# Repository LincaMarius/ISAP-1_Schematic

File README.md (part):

# ISAP-1 Computer Schematic
The ISAP-1 computer is the improved version of the SAP-1 computer made by me.

ISAP Computer stands for Improved Simple as Possible Computer

This is the stage of choosing the electronic components used to make the ISAP-1 computer and designing the Schematic.

By: Lincă Marius Gheorghe

https://github.com/LincaMarius

## About the project, brief description
The goal of this project is to create a more efficient version of the SAP (Simple As Possible) computer, but with minimal changes so that the instruction format remains the same.

This project is part of a project made by me:
https://github.com/LincaMarius/ISAP-Computer

where I optimized the SAP-1 computer

## ISAP-1 TTL Computer version 0.1
Version 0.1 of the ISAP-1 computer is based on the original SAP-1 computer schematic.

The structure of the SAP-1 computer and by implication the ISAP-1 computer is:

I want to make the ISAP-1 computer in modular form. So I modified the Structural Diagram like this:

It turns out that we will have the following modules:
- Reset and Clock
- ISAP-1 CPU
- Control Unit
- RAM Memory
- Output Display
- Back Plane

The SAP-1 computer was designed using 7400 series TTL chips in the LS (Low-Power Schottky) variant. Since version 0.1 of the ISAP-1 computer will be an almost identical copy of the SAP-1 computer, I will still use TTL technology.

I will keep the chip numbering order according to the original schematic of the SAP-1 computer.

### Central Processing Unit Schematic
The first module designed is the Central Processing Unit module.

The original block diagram of the Central Processing Unit of the SAP-1 computer and implicitly of the ISAP-1 computer is:

Initially, I used Altium Designer to design the Schematic and PCB.

But, so that this schematic can be viewed and possibly edited by anyone, I put the version edited with KiCAD on GitHub, because this program is free and can be freely used by anyone.

The implemented schematic will be almost identical to the original one of the SAP-1 Computer.

In the original schematic the chips are labeled C1 to C48. To eliminate confusion with the capacitor notation I have used the chip notation U1 to U49 as is used in modern days.

First I will implement the Central Processing Unit which has the following schematic:

You can see all the functional blocks in the diagram in figure 51. In addition I added decoupling capacitors for the power supply circuit. We also have the J1M connectors for connecting to the supply voltage given by the Back Plane, the J2M connector for connecting to the three system buses located on the Back Plane. The J3F and J4F connectors are used to allow the Control Block module to be attached to the CPU module.

#### Program Counter Schematic
In the original schematic, the authors used 4 Flip-Flops connected in such a way that they form a Binary Counter. For implementation, two 74LS107 were used for this purpose.

Counting is done when the CP control signal is active and the falling edge of the clock signal appears.

This action occurs for any instruction during [ microstep T2 ](https://github.com/LincaMarius/ISAP-1_Instruction_Set/blob/main/Pictures/Figure3.png).

The Program Counter has its output connected to the Bus, therefore it must be Tri-State. A 74LS126 chip is used for this purpose

The output is active only when the EP control signal is high.

This action occurs for any instruction during [ microstep T1 ](https://github.com/LincaMarius/ISAP-1_Instruction_Set/blob/main/Pictures/Figure3.png).

The Schematic does has no changes from the original one.

The original schematic has no decoupling capacitors for the chips. For the computer's operating speed of 1kHz this may not matter.

I added a 100nF decoupling capacitor for each chip used in order to eliminate high-frequency noise propagation along the power supply path.

#### Address Register Schematic
In the original schematic, the authors used a 4-bit register using the 74LS173 chip which has a permanently active output.

Note that the connection of the inputs to the data bus is in reverse order in the original SAP-1 computer schematic, D0 is connected to pin 11, D1 is connected to pin 12, D2 is connected to pin 13 and D4 is connected to pin 14.

The outputs are also connected in the reverse order. The operation of the SAP-1 computer is not affected by this order because the correspondence between inputs and outputs is maintained.

The current schematic has no changes from the original schematic.

I added a 100nF decoupling capacitor to the chip used in order to eliminate high-frequency noise propagation on the power supply path.

#### Instruction Register Schematic
The Instruction Register is made using two integrated circuits of the 74LS173 type which is a 4-bit register.

The first chip marked U8 in the diagram stores the upper nibble which represents the binary code of the instruction being executed.

The second chip marked in the diagram U9 stores the lower nibble which represents the parameter for the instruction being executed.

According to the datasheet for the 74LS173 chip, pin 14 is D0 and the corresponding output Q0 is pin 3, pin 13 is D1 and the corresponding output Q1 is pin 4, pin 12 is D2 and the corresponding output Q2 is pin 4, and pin 11 is D3 and the corresponding output Q3 is pin 6.

But in the SAP-1 computer schematic, pin 14 which is D0 and pin 3 which is Q0 are connected to bit 3 of the W Bus, pin 13 which is D1 and pin 4 which is Q1 are connected to bit 2 of the W Bus, pin 12 which is D2 and pin 5 which is Q2 are connected to bit 1 of the W Bus and pin 11 which is D3 and pin 6 which is Q3 are connected to bit 0 of the W Bus.

So, the order of inputs and outputs is reversed. Since the inputs and outputs are also reversed accordingly, the operation of the SAP-1 computer is normal.

The schematic does not present any changes from the original.

I added a 100nF decoupling capacitor for each chip used in order to eliminate high-frequency noise propagation along the power supply path.

#### Accumulator Register Schematic
The Accumulator register is made using two 4-bit 74LS173 type registers marked U10 and U11 in the diagram (in the original diagram they are marked C10 and C11).

Pin 1 and pin 2 are connected to ground which causes the outputs to be permanently active. Thus, the contents of the Accumulator Register are permanently transmitted to the ALU via signals AD0 to AD7.

The contents of the Accumulator Register are put on the bus when the EA control signal is active, which activates the 8 Tri-State drivers. The Tri-State drivers are implemented using two 74LS126 chips, each containing 4 Tri-State drivers.

As in the previous cases, the order of inputs and outputs is reversed from the order of the bits on the W bus. Since the inputs and outputs are also reversed accordingly, the operation of the SAP-1 computer is normal.

The schematic has no changes from the original.

I added a 100nF decoupling capacitor for each chip used in order to eliminate high-frequency noise propagation along the power supply path.

#### Adder / Subtractor Schematic
The SAP-1 computer has no Logic Unit, it can only perform the Addition and Subtraction operations.

The main element of the Arithmetic Unit is the 74LS83 chip which is a 4-bit Full Adder, so two such chips are used.

The Subtract Operation is performed by 2's Complementing the operand B. For this purpose, 8 x XOR Gates are used. Each 74LS86 chip has 4 gates, so 2 chips are used.

The result is transmitted on the Bus via 8 three-state buffers when the EU control signal is active. These buffers are of the 74LS126 type. Each chip has 4 buffers, so 2 chips are required.

The schematic has no changes from the original.

I added a 100nF decoupling capacitor for each chip used in order to eliminate high-frequency noise propagation along the power supply path.

#### Register B Schematic
Register B acts as a temporary storage register, where the operand B required by the Adder to perform the Addition operation is loaded.

In the original schematic, two 4-bit 74LS173 type registers labeled C20 and C21 are used.

When the LB control signal is low and the rising edge of the clock signal occurs, the data present on the Bus is loaded into the registers.

The output is connected to input B of the Adder and is permanently enabled by connecting pins 1 and 2 to ground.

The schematic has no changes from the original.

I added a 100nF decoupling capacitor for each chip used in order to eliminate high-frequency noise propagation along the power supply path.

The archived project for ISAP-1 TTL Computer version 0.1 is here: \
https://github.com/LincaMarius/ISAP-1_Schematic/blob/main/KiCAD/ ISAP-1_TTL_CPU_1_0.zip

### Control Unit Schematic
The Control Unit's role is to direct the flow of data between the various Blocks of the Computer to ensure its operation and achieve the expected results.

It consists of three elements: the Instruction Decoder, the Ring Counter and the Control Matrix as can be seen in figure 14:

### Output Device – Binary Display
In the SAP-1 computer the output device is called the Output Register and is present in the Block Diagram at the bottom right of the drawing.

The Binary Display is made with 8 LEDs connected directly to the output of the Output Register.

### Output Device Schematic
In the original schematic, two 4-bit 74LS173 registers are used, denoted C22 and C23.

When the I/O control signal (the original LO) is low and the rising edge of the clock signal appears, the data present on the Bus is loaded into the registers.

The output is permanently active because pins 1 and 2 are connected to ground. The outputs are labeled O0 to O7.

I added the connectors marked J2_1 and J2_2 for connection to the Base PCB in case the Binary Display PCB separates from the computer PCB.

The schematic does not present any other changes compared to the original one.

### Binary Display Schematic
The Binary Display consists of eight LEDs connected to eight current limiting resistors of 1k ohm each.

The current is limited by resistors for a red LED to the value of (Voh – Vled) / (R + Rint) = (2.4V – 1.8V) / (1000 + 100) = 0.5 / 1100 = 0.5mA (theoretical).

I added the connectors marked J2_1 and J2_2 for connection to the Base PCB in case the Binary Display PCB separates from the computer PCB.

The schematic does not present any other changes compared to the original one.

### Front Panel Schematic
The Front Panel provides the user interface. Contains the Reset circuit, Manual/Automatic mode selector, Step button, main clock.

I added two connectors marked J5_1 and J5_2 for connection to the Base PCB in case the Front Panel PCB is separated and used separately from the ISAP-1 computer PCB.

The switches can be mounted on this PCB or mounted on a Front Panel and connected via wires.

The schematic does not present any other changes compared to the original one.

The switches used to set the Memory in Programming mode must also be placed on the Front Panel.

The switches can be mounted on this module or mounted on a Front Panel and connected via wires.

### Control Unit Schematic
The Control Unit's role is to direct the flow of data between the various Blocks of the Computer to ensure its operation and achieve the expected results.

It consists of three elements: the Instruction Decoder, the Ring Counter and the Control Matrix as can be seen in figure 17:

The schematic does not present any other changes compared to the original one.

### Power Supply Schematic 
The power supply's role is to provide the 5 Volt supply voltage and support the computer's power consumption.

This power supply is powered directly from the Mains and consists of a step-down transformer followed by a full bridge rectifier and an integrated regulator of 5 Volts.

The transformer according to the Bill of Materials is of the F-25X type and has a primary voltage of 115 Volts, but in Europe a transformer with a primary voltage of 230 Volts is required.

The secondary voltage according to the Materials List on page 502 in the original book is 12.6 Volts. Nowadays we can buy standard transformers with a secondary voltage of 12 Volts.

The secondary current is a maximum of 1.5 Amps according to the same description.

The nominal power of the transformer for a current consumption of maximum 1.5 Amps is 12V x 1.5A = 18 VA.

The maximum voltage on capacitor C68 is: Vmax = Vsec * 1.41 – 2 * Vd = 12 * 1.414 – 2 * 0.8 = 16.97 – 1.6 = 15.37 Volts

Therefore, capacitor C68 must have a working voltage of 25 Volts.

The voltage ripple on the filter capacitor C68 is: dU = (Iout * T) / (2 * C3)

For a mains voltage frequency of 50 Hz we have T = 1/f = 1/50 = 0.02 s

For a mains voltage frequency of 60 Hz we have T = 1/f = 1/50 = 0.017 s

Since we have a double alternating rectification the pulsation frequency is doubled, so the period is halved

Thus the ripple period is: T = 0.01s for mains voltage with a frequency of 50 Hz and T = 0.0083s for mains voltage with a frequency of 60 Hz.

The voltage ripple on the filter capacitor C68 is: dU = (1.5A * 0.01s) / (2 * 0.001F) = 0.015 / 0.002 = 7.5 Volts for mains voltage with a frequency of 50 Hz.

The voltage ripple on the filter capacitor C68 is: dU = (1.5A * 0.0083s) / (2 * 0.001F) = 0.01245 / 0.002 = 6.225 Volts for mains voltage with a frequency of 60 Hz.

The minimum voltage on the filter capacitor C68 is: Vmin = Vmax – dU = 15.37V – 7.5V = 7.87 Volts for mains voltage with a frequency of 50 Hz.

The minimum voltage on the filter capacitor C68 is: Vmin = Vmax – dU = 15.37V – 6.225V = 9.145 Volts for mains voltage with a frequency of 60 Hz.

The average voltage on the filter capacitor C68 is: V = Vmax – dU/2 = 15.37V – 7.87V/2 = 15.37V – 3.935V = 11.435 Volts for mains voltage with a frequency of 50 Hz.

The average voltage on the filter capacitor C68 is: V = Vmax – dU/2 = 15.37V – 6.225V/2 = 15.37V – 3.1125V = 12.2575 Volts for mains voltage with a frequency of 60 Hz.

The maximum power dissipated by the LM340T-5 or LM7805 integrated regulator is: P = (Vin – Vout) * I = (11.435V – 5V) * 1.5A = 6.435V * 1.5A = 9.66 Watts for mains voltage with a frequency of 50 Hz.

The maximum power dissipated by the LM340T-5 or LM7805 integrated regulator is: P = (Vin – Vout) * I = (12.2575V – 5V) * 1.5A = 7.2575V * 1.5A = 10.87 Watts for mains voltage with a frequency of 60 Hz.

To dissipate this power, we have provided a radiator to cool the integrated stabilizer. Otherwise, it will go into overtemperature protection.

I added a 100nF ceramic capacitor to the input and output of the integrated voltage regulator to meet the stability requirements according to the datasheet data.

The schematic does not present any other changes compared to the original one.

### ISAP-1 TTL SBC assembly
To power the computer with 5 volts, I included a Barrel Jack.

The schematic does not present any other changes compared to the original one.

An overview of the PCB for the Single Board Computer variant of the ISAP-1 Computer is shown in the following figure:

An overview for the ISAP-1 TTL SBC Computer is shown in the following figure:

The ISAP-1 computer project made in KiCAD is here: \
https://github.com/LincaMarius/ISAP-1_Schematic/tree/main/KiCAD/ISAP1_TTL_SBC_ver1_0.zip

*A total of 48 chips were used to implement this version of the ISAP-1 computer.*

## ISAP-1 Model A Version 1.1
In Version 1.1, an improvement is made to the ISAP-1 computer by implementing the Variable Machine Cycle.

The Instruction Set remains unchanged but the Control Block implementation changes.

In the book on page 163 the authors present a method of improving the SAP-1 Computer by implementing the Variable Machine Cycle.

The schematic is shown in Figure 10-17 and consists of 5 inverters and a 12-input NAND gate that generates the #NOP signal when the Control Block output has the NOP instruction encoded in Hexadecimal as 3E3h and a two-input AND gate that resets the Ring Counter when the #NOP or #CLR signal is low. 

We can note that the SAP-1 Computer schematic is not modified to implement this functionality, only two logic gates are added.

### Control Block Update
Version 1.1 of the ISAP-1 computer presents the modification of the Control Block as described by the authors, which implements Variable Length Microcode.

The schematic is modified by adding 2 gates and 5 inverters, but it is not necessary to redesign the computer.

The starting point is the Control Block diagram of version 1.0 shown in figure 15.

The scheme presented in the book to be implemented is intended for a control matrix made with ROM memory.

Because in the current version we use logic gates to implement the control matrix, we have greater freedom to select the signals we are interested in.

The signals CP, PE, EA, SI and EU must be inverted.

The CP signal is T2 and must be inverted.

The EP signal is T1, so the inverted EP is the inverted T1. This is available at the output of the inverter U35E.

The EA signal is the output of gate U42A inverted by U35F, so if EA is inverted once more it is the same signal as that available before the double inversion, i.e. the signal from the output of gate U42A can be used directly without inversion.

The SU signal is the output of gate U42B inverted by U48A, so if SU is inverted once more it is the same signal as that available before the double inversion, i.e. the signal from the output of gate U42B can be used directly without inversion.

The EU signal is the output of gate U42B and must be inverted.

In conclusion, only the CP and EU signals need to be inverted.

All of these signals act as inputs to a 12-input NAND gate.

For implementation, a 12-input NAND gate of the 74S134 type, a 13-input NAND gate of the 74ALS133 type can be used.

Another variant is using:
- one 8-input NAND part of the 74LS30 type, one 4-input NAND part of the 74LS20 type and one 2-input OR part of the 74LS32 type
- three 4-input NAND parts of the 74LS20 type, one 3-input NOR part of the 74LS27 type and one 74LS04 type inverter
- four 3-input NAND parts of the 74LS10 type, one 4-input NOR part of the 74LS29 type and one 74LS04 type inverter
- or six 2-input NAND parts of the 74LS00 type, three 3-input NOR parts of the 74LS27 type and one 74LS04 type inverter

I implemented the new version using the available logic gates that were not used by the authors of the book, so I added only one chip.

I used the U48B inverter and the U48C inverter to invert the CP and EU signals.

I used the 74LS133 chip which is a 13-input NAND gate.

For the reset signal control, instead of adding a new 74LS08 chip to use a single AND logic gate, I used an available two-input 74LS00 NAND gate marked U43D and inverted its output signal with the U48D inverter.

The Control Block schematic of the ISAP-1 Model A Version 1.1 computer is shown in the following figure:

This is what the completed PCB looks like for ISAP-1 Model A Version 1.1

An overview of the PCB is shown in the following figure

The ISAP-1 Model A Version 1.1 computer project made in KiCAD is here: \
https://github.com/LincaMarius/ISAP-1_Schematic/blob/main/KiCAD/ISAP-1_modelA_ver1_1.zip

*A total of 49 chips were used to implement this version of the ISAP-1 computer. One more than in the previous implementation.*

## ISAP-1 Model B version 1.0
Revision B of the ISAP-1 computer presents the modification of the Control Block as described by the authors, whereby the hard-wired logic is replaced with programmed logic.

In previous implementations, 18 chips were used in the Control Block.

One solution for implementation at the time the card was published in 1975 was to use the 74S188 (32 x 8 PROM open-collector), 74S288 (32 x 8 PROM tree-state), 74S387 (256 x 4 PROM open-collector), 74S287 (256 x 4 PROM tree-state), 74S470 (256 x 8 PROM open-collector), 74S471 (256 x 8 PROM tree-state), 74S473 (512 x 8 PROM open-collector), 74S472 (512 x 8 PROM tree-state), 74S475 (512 x 8 PROM open-collector), 74S474 (512 x 8 PROM tree-state), 74S451 (1024 x 8 PROM open-collector), 74S450 (1024 x 8 tree-state PROM), 74S479 (1024 x 8 open-collector PROM), 74S478 (1024 x 8 tree-state PROM), 74S3708 (1024 x 8 open-collector PROM), 74S2708 (1024 x 8 tree-state PROM), 74S477 (1024 x 4 open-collector PROM), 74S476 (1024 x 4 tree-state PROM).

But these chips are no longer manufactured and even if we could find one we would not be able to program it because it requires a programmer built specifically for this purpose. These PROMs are programmable only once and cannot be reprogrammed. They use tungsten fuses to store information and require a programming current of 150mA.

A modern solution is the use of PROM, EPROM, EPROM-OTP, EEPROM, FLASH memories

For me the best solution is to use an EEPROM or FLASH memory because they allow the information to be rewritten many times which leads to the possibility of improving the final product over time.

In the current implementation scheme of revision B in the Control Block, 10 chips were used

The schematic uses 8k EPROMs, but any type of ROM of any capacity can be used with minor modifications.

This is what the completed PCB looks like for ISAP-1 Model B Version 1.0

An overview of the PCB is shown in the following figure

The ISAP-1 Computer Model B version 1.0 project made in KiCAD is here: \
https://github.com/LincaMarius/ISAP-1_Schematic/blob/main/KiCAD/ISAP-1_modelB_ver1_0.zip

A total of 40 chips were used to build the ISAP-1 Model B Version 1.0 computer. Compared to the ISAP-1 Model A Version 1.0 where 49 were used, we have a reduction in the number of chips by 9 pieces while maintaining the same functionality of the computer.

## ISAP-1 Model B Version 1.1
Revision B of the ISAP-1 computer presents the modification of the Control Block as described by the authors, whereby the hard-wired logic is replaced with programmed logic.

In Version 1.1, an improvement is made to the ISAP-1 computer by implementing the Variable Machine Cycle.

The Instruction Set remains unchanged but the Control Block implementation changes.

In the book on page 163 the authors present a method of improving the SAP-1 Computer by implementing the Variable Machine Cycle.

The schematic is shown in Figure 10-17 and consists of 5 inverters and a 12-input NAND gate that generates the #NOP signal when the Control Block output has the NOP instruction encoded in Hexadecimal as 3E3h and a two-input AND gate that resets the Ring Counter when the #NOP or #CLR signal is low. 

The starting point is the Control Block diagram of version 1.0 shown in figure 23.

The scheme presented in the book that needs to be implemented is for a control matrix made with ROM memory with a capacity of 16 x 12 bits. So we only have 12 outputs that are used for control.

The signals CP, PE, EA, SI and EU must be inverted.

All of these signals act as inputs to a 12-input NAND gate.

For implementation, a 12-input NAND gate of the 74S134 type, a 13-input NAND gate of the 74ALS133 type can be used.

I implemented the new version using available logic gates that were not used by the authors of the book, so I added two chips. I used an unused 74LS00 NAND gate and an inverter to make the AND gate in the Ring Counter Reset circuit.

I used the 74LS133 chip which is a 13-input NAND gate.

In the current implementation scheme of revision B in the Control Block, 12 chips were used

The Control Block schematic of the ISAP-1 Model B Version 1.1 Computer is shown in the following figure:

This is what the completed PCB looks like for ISAP-1 Model B Version 1.1

An overview of the PCB is shown in the following figure

The ISAP-1 Model B Version 1.1 computer project made in KiCAD is here: \
https://github.com/LincaMarius/ISAP-1_Schematic/blob/main/KiCAD/ISAP-1_modelB_ver1_1.zip

A total of 42 chips were used to build the ISAP-1 Model B Version 1.1 computer. Compared to the ISAP-1 Model A Version 1.0 where 49 were used, we have a reduction in the number of chips by 7 pieces while maintaining the same functionality of the computer.

## ISAP-1 Model B Version 1.2
In this version I will modify the ISAP-1 Computer by changing it from a Single Board Computer to a modular version.

The functionality of the Computer does not change and the Instruction Set does not change.

Since the SAP-1 Computer does not have decoupling capacitors provided in the original schematic, I will make improvements to the electronic schematic by adding decoupling capacitors for each chip used.

Since the SAP-1 Computer was originally designed in 1975, the power supply uses a mains transformer and a Linear Voltage Regulator. This technology is specific to that time period.

Nowadays, building such a power supply is more expensive compared to modern switching power supplies that are easily available. The purchase price of just the mains transformer is comparable to the purchase price of a modern 5 Volt power supply.

Therefore, I will remove the original power supply from the Project and the Computer will be powered using an external 5 Volt source. This will reduce the overall size and weight of the Computer.

### Program Counter
The schematic and functionality are unchanged from the original. I added decoupling capacitors with a value of 100 nF for each chip used.

For example, for 74LS107 the High to Low switching time is normally 15 ns. This time is desired as small as possible to have a high working speed of the Computer. So if we consider the transition as half a period of a signal we obtain a maximum period of 30 ns. This corresponds to a frequency of 33 MHz. At these frequencies the wires on the PCB behave as inductances and will increase the switching time. To eliminate this phenomenon we put decoupling capacitors as close as possible to the power pins of the chip.

The new schematic for the Program Counter Block is:

### Address Register
The schematic and functionality are unchanged from the original. I added a decoupling capacitor with a value of 100 nF for the chip used.

The new Address Register schematic is:

### Instruction Register
The schematic and functionality are unchanged from the original. I added decoupling capacitors with a value of 100 nF for each chip used.

I also added a 10 uF filter capacitor to filter out low frequency noise that may appear on the power supply circuit.

The new schematic for the Instruction Register is:

### Accumulator Register
The schematic and functionality are unchanged from the original. I added decoupling capacitors with a value of 100 nF for each chip used.

I also added a 10 uF filter capacitor to filter out low frequency noise that may appear on the power supply circuit.

The new schematic for the Accumulator Register is:

### Arithmetic Unit
The schematic and functionality are unchanged from the original. I added decoupling capacitors with a value of 100 nF for each chip used.

I also added a 100 uF filter capacitor to filter out low frequency noise that may appear on the power supply circuit.

The new schematic for the Arithmetic Unit is:

### Register B
The schematic and functionality are unchanged from the original. I added decoupling capacitors with a value of 100 nF for each chip used.

I also added a 10 uF filter capacitor to filter out low frequency noise that may appear on the power supply circuit.

The new schematic for Register B is:

All these Modules are part of the Central Processing Unit of the ISAP-1 Model B Version 1.2 Computer

This is what the completed PCB looks like for the Central Processing Unit of ISAP-1 Computer Model B Version 1.2

An overview of the completed PCB for the ISAP-1 Model B Version 1.2 Central Processing Unit is as follows

At the bottom of the PCB we have the 4-pin J1 connector for 5V power supply and the 40-pin J2 connector for connection to the Bus.

To reduce the size of the CPU module I decided to make the Control Block as an independent Module that will attach to the CPU Module like an extension.

The connection between the CPU Module and the Control Unit Module is made through two 15-pin connectors each marked J3 and J4.

By physically separating the Control Unit into an independent Module, it has the major advantage that for modifying the Instruction Set, most changes are made at the Control Block level while the rest of the modules remain unchanged.

### Control Unit
The Control Unit's role is to direct the flow of data between the various Component Blocks of the Computer to ensure its operation and achieve the expected results.

It consists of three elements: the Instruction Decoder, the Ring Counter, and the Control Matrix.

The ISAP-1 Model B computer has a Control Matrix made with ROM memories.

For the current version of the ISAP-1 Computer to be modular, the CPU portion must be made on a single PCB. Since the CPU consists of many chips, I decided to divide its construction into two separate PCBs that will sit back to back.

We will have one PCB that contains all the building blocks of the CPU part and the second PCB contains only the Control Block.

Therefore, the Control Block will be treated as an independent module within the ISAP-1 Computer.

For connection to the CPU base module, we have provided two 10-pin connectors each, marked in the diagram as J3 and J4.
These will be mounted on the back of the PCB.

The functionality does not change from the original. I added decoupling capacitors with a value of 100 nF for each chip used.

I also added a 220 uF filter capacitor to filter out low frequency noise that may appear on the power supply circuit.

The new schematic for the Control Unit is:

This is the finished PCB layout for the Control Block Module of ISAP-1 Model B Computer Version 1.2

An overview of the completed PCB for the ISAP-1 Model B Computer Control Block Module Version 1.2 is as follows

To indicate the wrong mounting position of this module, I positioned the J3 connector on the PCB offset from the J4 connector.

If the module is mounted upside down due to the gap between the pins we will not have the alignment of the PCBs at the top. Normally the two PCBs should be at the same level at the top

### Memory Module
The modular version of the ISAP-1 Computer allows us to implement the Memory as an independent Module with its own PCB

Now all switches used for memory programming have been moved to the Front Panel Module

The functionality is unchanged from the original. I added a 100 nF decoupling capacitor for the chip used.

I also added a 10 uF filter capacitor to filter out low frequency noise that may appear on the power supply circuit.

This module communicates with the rest of the computer through the three System Buses. To connect the module to the buses, I added a connector marked J7 in the diagram.

To prevent the Module from being mounted in the wrong orientation, which would lead to its failure, we added a special power connector offset from the Bus connector by 14 mm.

The new schematic for the ISAP-1 Model B Computer Memory Module Version 1.2 is:

This is the finished PCB layout for the Memory Module of ISAP-1 Model B Computer Version 1.2

An overview of the completed PCB for the ISAP-1 Model B Version 1.2 Computer Memory Module is as follows

### Output Register Module
The modular version of the ISAP-1 Computer allows us to implement the Output Register as an independent Module with its own PCB

The schematic and functionality are unchanged from the original. I added a 100 nF decoupling capacitor for the chip used.

I also added a 100 uF filter capacitor to filter out low frequency noise that may appear on the power supply circuit.

This module communicates with the rest of the computer through the three system buses. To connect the module to the buses, I added a connector marked J9 in the diagram.

To prevent the Module from being mounted in the wrong orientation, which would lead to its failure, I added a special power connector offset from the Bus connector by 14 mm, marked J8 in the diagram. The Module will stand vertically in the ISAP-1 Computer

The Binary Display is designed as a separate Module and connects to the Output Register Module via the 10-pin connector marked J10 in the schematic.

The new schematic for the Output Register Module for the ISAP-1 Model B Computer Version 1.2 is:

This is the finished PCB layout for the Output Register Module of ISAP-1 Model B Computer Version 1.2

An overview of the completed PCB for the ISAP-1 Model B Version 1.2 Computer Output Register Module is as follows

### Binary Display Module
The modular version of the ISAP-1 Computer allows us to implement the Binary Display as an independent Module with its own PCB

The schematic and functionality are unchanged from the original. 

The Binary Display is designed as a separate Module and connects to the Output Register Module via the 10-pin connector marked J10 in the schematic.

The new schematic for the Binary Display Module for the ISAP-1 Model B Computer Version 1.2 is:

This is the finished PCB layout for the Binary Display Module of ISAP-1 Model B Computer Version 1.2

An overview of the completed PCB for the ISAP-1 Model B Version 1.2 Binary Computer Display Module is as follows

### Front Panel Module
The modular version of the ISAP-1 Computer allows us to implement the Front Panel as an independent Module with its own PCB

The schematic and functionality are unchanged from the original. I added a 100 nF decoupling capacitor for the chip used.

I also added a 22 uF filter capacitor to filter out low frequency noise that may appear on the power supply circuit.

This module communicates with the rest of the computer through the three system buses. To connect the module to the buses, I added a connector marked J12 in the diagram.

To prevent the Module from being mounted in the wrong orientation, which would lead to its failure, I added a special power connector offset from the Bus connector by 14 mm, marked J11 in the diagram. The Module will stand vertically in the ISAP-1 Computer

I designed this module to be positioned in position 1 on the BackPlane. This module will sit horizontally when attached to the BackPlane.

The new schematic for the Front Panel Module for the ISAP-1 Model B Computer Version 1.2 is:

This is the finished PCB layout for the Front Panel Module of ISAP-1 Model B Computer Version 1.2

An overview of the completed PCB for the ISAP-1 Model B Computer Front Panel Module Version 1.2 is as follows

### Backplane Module
The modular version of the ISAP-1 Computer allows us to implement the Backplane as an independent Module with its own PCB

This module is an addition to the original scheme and is intended to ensure the modularity of the Computer.

I also added a 100 uF filter capacitor to filter out low frequency noise that may appear on the power supply circuit.

The LED marked D9 signals the presence of supply voltage. The current limiting resistor is calculated as follows:

R11 = (Vcc – VF) / I_Led = (5V – 1.8V) / 15mA = 3.2V / 0.015A =  213 Ohms

The closest standard value is 220 Ohm. VF = 1.8V was used to drive a red LED.

The communication of all modules is done through the three buses (Address Bus, Data Bus and Command Bus) for which 7 40-pin connectors are provided, which are associated with 7 4-pin connectors for the 5 Volt power supply.

To prevent the Modules from being mounted in the wrong orientation, which would lead to their failure, I added this power connector offset from the Bus connector.

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
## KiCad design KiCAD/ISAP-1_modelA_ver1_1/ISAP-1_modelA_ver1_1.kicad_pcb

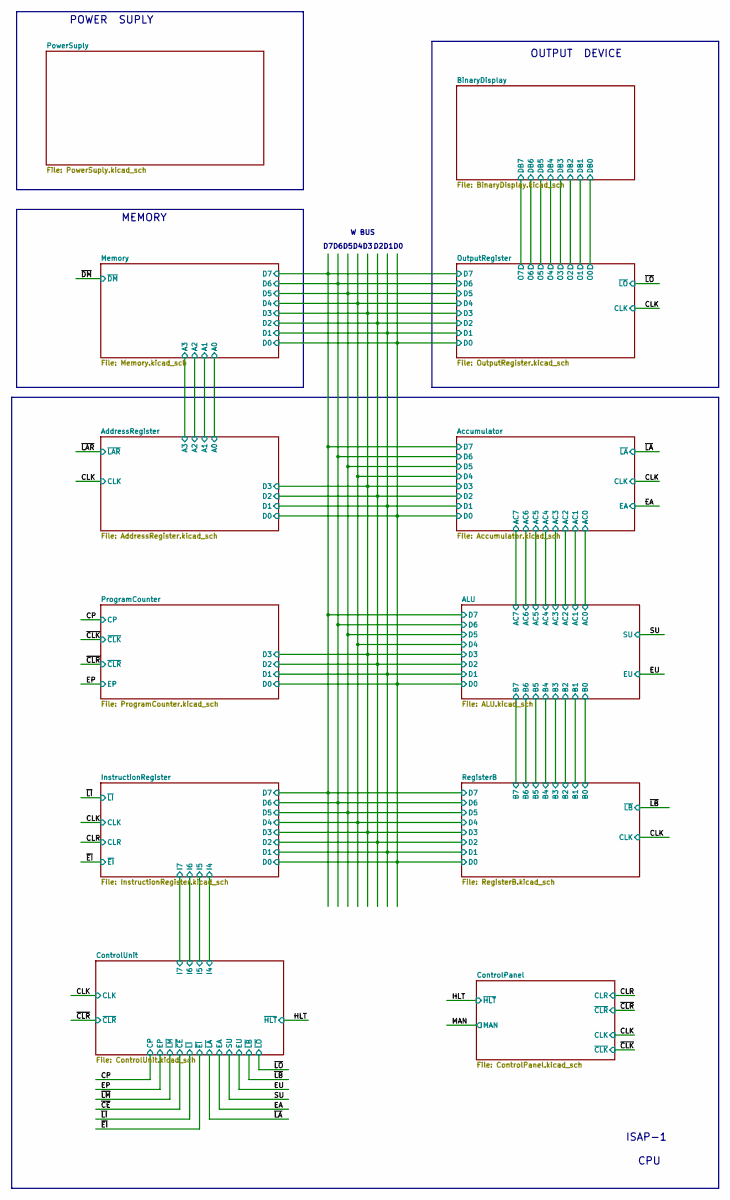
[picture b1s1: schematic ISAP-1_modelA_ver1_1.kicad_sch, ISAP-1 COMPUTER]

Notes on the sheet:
POWER SUPLY
ISAP-1 CPU
W BUS
MEMORY
OUTPUT DEVICE

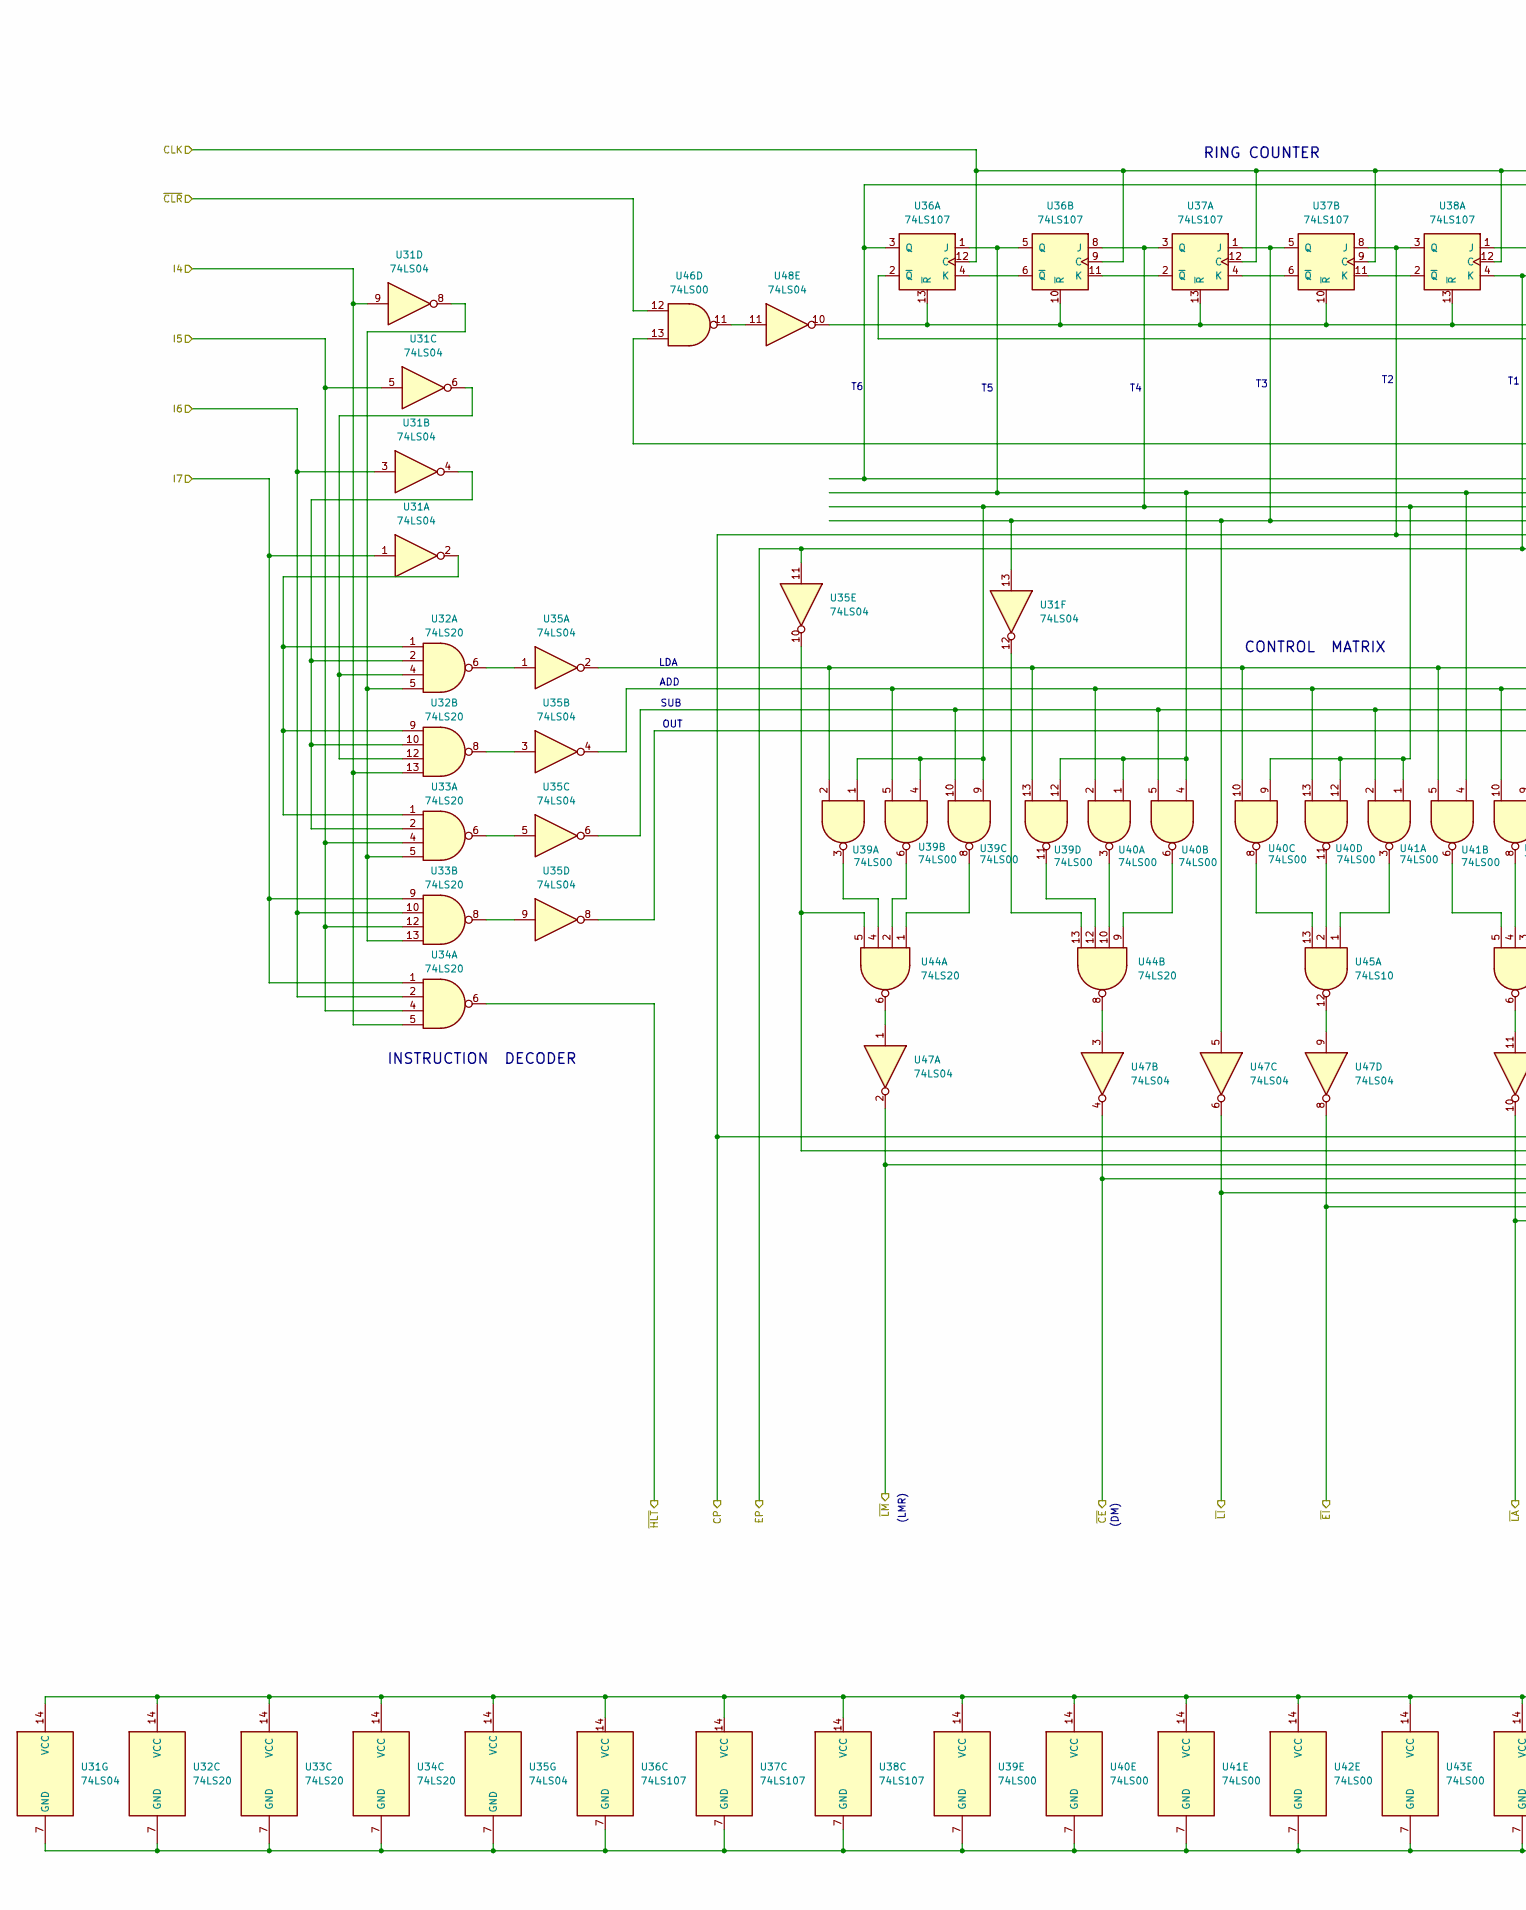
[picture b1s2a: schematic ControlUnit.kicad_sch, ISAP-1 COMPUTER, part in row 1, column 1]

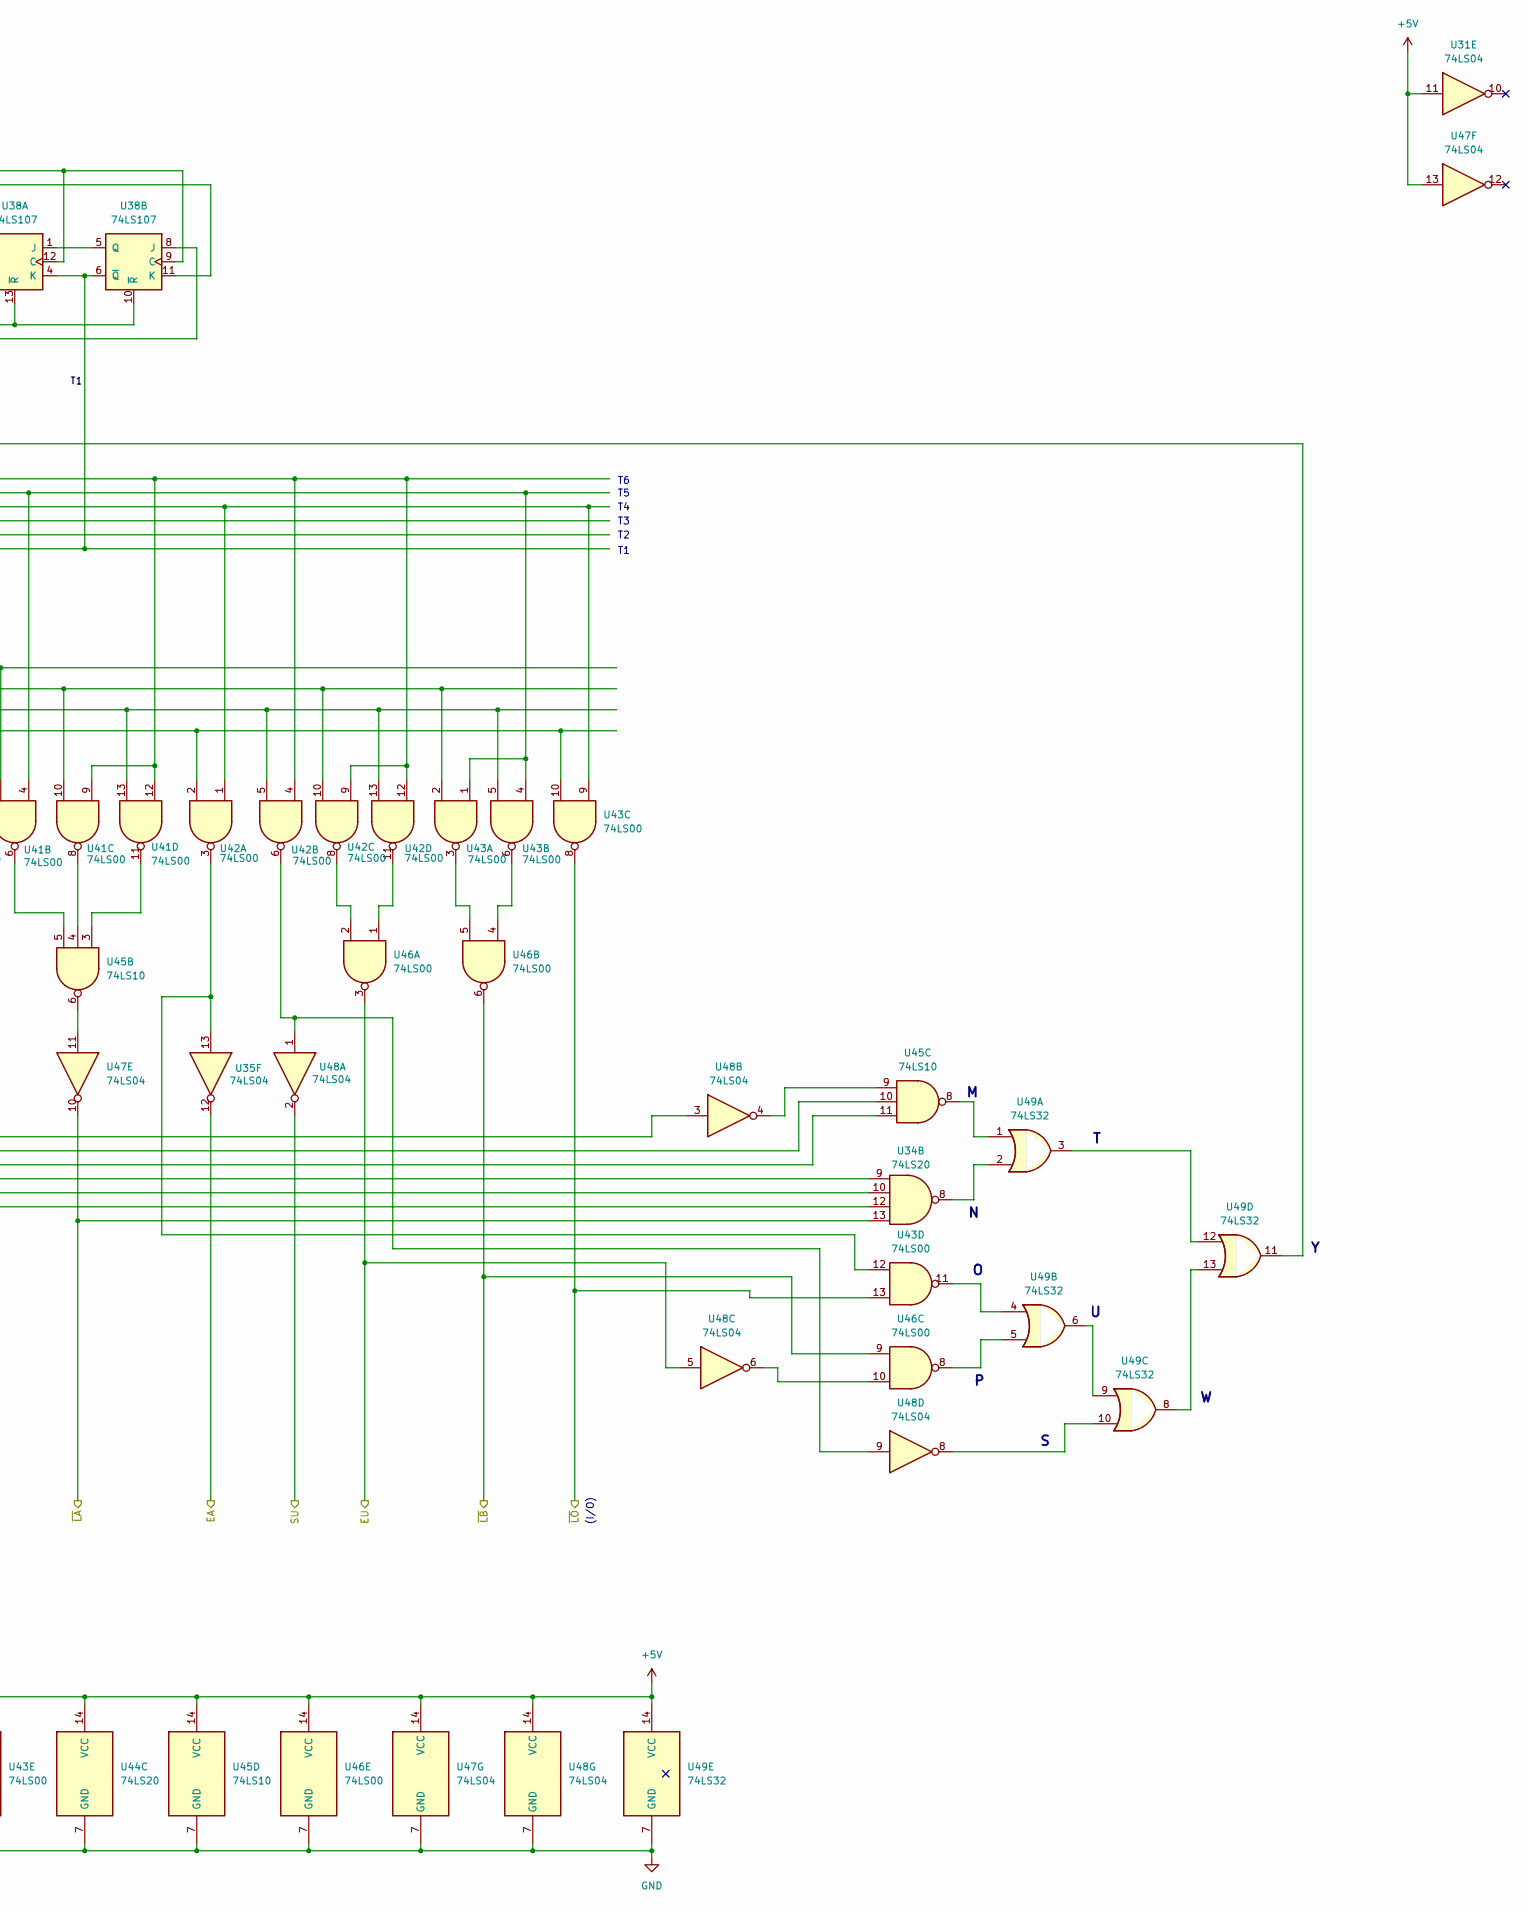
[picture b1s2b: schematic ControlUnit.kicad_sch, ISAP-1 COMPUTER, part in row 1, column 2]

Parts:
U31, U35, U47, U48: 74LS04; DIP-14_W7.62mm_LongPads
U32, U33, U34, U44: 74LS20; DIP-14_W7.62mm_LongPads
U36, U37, U38: 74LS107; DIP-14_W7.62mm_LongPads
U39, U40, U41, U42, U43, U46: 74LS00; DIP-14_W7.62mm_LongPads
U45: 74LS10; DIP-14_W7.62mm_LongPads
U49: 74LS32; DIP-14_W7.62mm

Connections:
+5V: U31.11, U31.14 (VCC), U32.14 (VCC), U33.14 (VCC), U34.14 (VCC), U35.14 (VCC), U36.14 (VCC), U37.14 (VCC), U38.14 (VCC), U39.14 (VCC), U40.14 (VCC), U41.14 (VCC), U42.14 (VCC), U43.14 (VCC), U44.14 (VCC), U45.14 (VCC), U46.14 (VCC), U47.13, U47.14 (VCC), U48.14 (VCC), U49.14 (VCC); also elsewhere on the board
/CLK: U36.9 (C), U36.12 (C), U37.9 (C), U37.12 (C), U38.9 (C), U38.12 (C); also elsewhere on the board
/CP: U37.8 (J), U38.3 (Q), U48.3; also elsewhere on the board
/ControlUnit/I4: U31.9, U32.13, U34.5; also elsewhere on the board
/ControlUnit/I5: U31.5, U33.4, U33.12, U34.4; also elsewhere on the board
/ControlUnit/I6: U31.3, U33.10, U34.2; also elsewhere on the board
/ControlUnit/I7: U31.1, U33.9, U34.1; also elsewhere on the board
/EA: U35.12; also elsewhere on the board
/EP: U35.11, U38.4 (K), U38.6 (~Q); also elsewhere on the board
/EU: U46.3, U48.5; also elsewhere on the board
/HLT: U34.6; also elsewhere on the board
/SU: U48.2; also elsewhere on the board
/~CE: U34.9, U47.4
/~CLR: U46.12; also elsewhere on the board
/~EI: U34.12, U47.8; also elsewhere on the board
/~LA: U34.13, U47.10; also elsewhere on the board
/~LB: U46.6, U46.9; also elsewhere on the board
/~LI: U34.10, U47.6; also elsewhere on the board
/~LM: U45.11, U47.2
/~LO: U43.8, U43.13; also elsewhere on the board
GND: U31.7 (GND), U32.7 (GND), U33.7 (GND), U34.7 (GND), U35.7 (GND), U36.7 (GND), U37.7 (GND), U38.7 (GND), U39.7 (GND), U40.7 (GND), U41.7 (GND), U42.7 (GND), U43.7 (GND), U44.7 (GND), U45.7 (GND), U46.7 (GND), U47.7 (GND), U48.7 (GND), U49.7 (GND); also elsewhere on the board
unnamed: U31.2, U32.1, U32.9, U33.1
unnamed: U31.4, U32.2, U32.10, U33.2
unnamed: U31.6, U32.4, U32.12
unnamed: U31.8, U32.5, U33.5, U33.13
unnamed: U31.12, U44.13
unnamed: U32.6, U35.1
unnamed: U32.8, U35.3
unnamed: U33.6, U35.5
unnamed: U33.8, U35.9
unnamed: U34.8, U49.2
unnamed: U35.2, U39.2, U39.13, U40.10, U41.5
unnamed: U35.4, U39.5, U40.2, U40.13, U41.10, U42.10, U43.2
unnamed: U35.6, U39.10, U40.5, U41.2, U41.13, U42.5, U42.13, U43.5
unnamed: U35.8, U42.2, U43.10
unnamed: U35.10, U44.5, U45.10
unnamed: U35.13, U42.3, U43.12
unnamed: U36.1 (J), U36.5 (Q), U39.12, U40.1, U40.4, U41.4, U43.1, U43.4
unnamed: U36.4 (K), U36.6 (~Q)
unnamed: U36.3 (Q), U38.11 (K), U41.9, U41.12, U42.4, U42.9, U42.12
unnamed: U36.2 (~Q), U38.8 (J)
unnamed: U36.10 (~R), U36.13 (~R), U37.10 (~R), U37.13 (~R), U38.10 (~R), U38.13 (~R), U48.10
unnamed: U36.8 (J), U37.3 (Q), U39.1, U39.4, U39.9, U40.9, U40.12, U41.1, U42.1, U43.9
unnamed: U36.11 (K), U37.2 (~Q)
unnamed: U31.13, U37.1 (J), U37.5 (Q), U47.5
unnamed: U37.4 (K), U37.6 (~Q)
unnamed: U37.11 (K), U38.2 (~Q)
unnamed: U38.1 (J), U38.5 (Q)
unnamed: U39.3, U44.4
unnamed: U39.6, U44.2
unnamed: U39.8, U44.1
unnamed: U39.11, U44.12
unnamed: U40.3, U44.10
unnamed: U40.6, U44.9
unnamed: U40.8, U45.13
unnamed: U40.11, U45.2
unnamed: U41.3, U45.1
unnamed: U41.6, U45.5
unnamed: U41.8, U45.4
unnamed: U41.11, U45.3
unnamed: U42.6, U48.1, U48.9
unnamed: U42.8, U46.2
unnamed: U42.11, U46.1
unnamed: U43.3, U46.5
unnamed: U43.6, U46.4
unnamed: U43.11, U49.4
unnamed: U44.6, U47.1
unnamed: U44.8, U47.3
unnamed: U45.6, U47.11
unnamed: U45.8, U49.1
unnamed: U45.9, U48.4
unnamed: U45.12, U47.9
unnamed: U46.8, U49.5
unnamed: U46.10, U48.6
unnamed: U46.11, U48.11
unnamed: U46.13, U49.11
unnamed: U48.8, U49.10
unnamed: U49.6, U49.9
unnamed: U49.3, U49.12
unnamed: U49.8, U49.13

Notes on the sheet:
(DM)
(LMR)
(I/O)
CONTROL MATRIX
INSTRUCTION DECODER
ADD
SUB
LDA
OUT
RING COUNTER

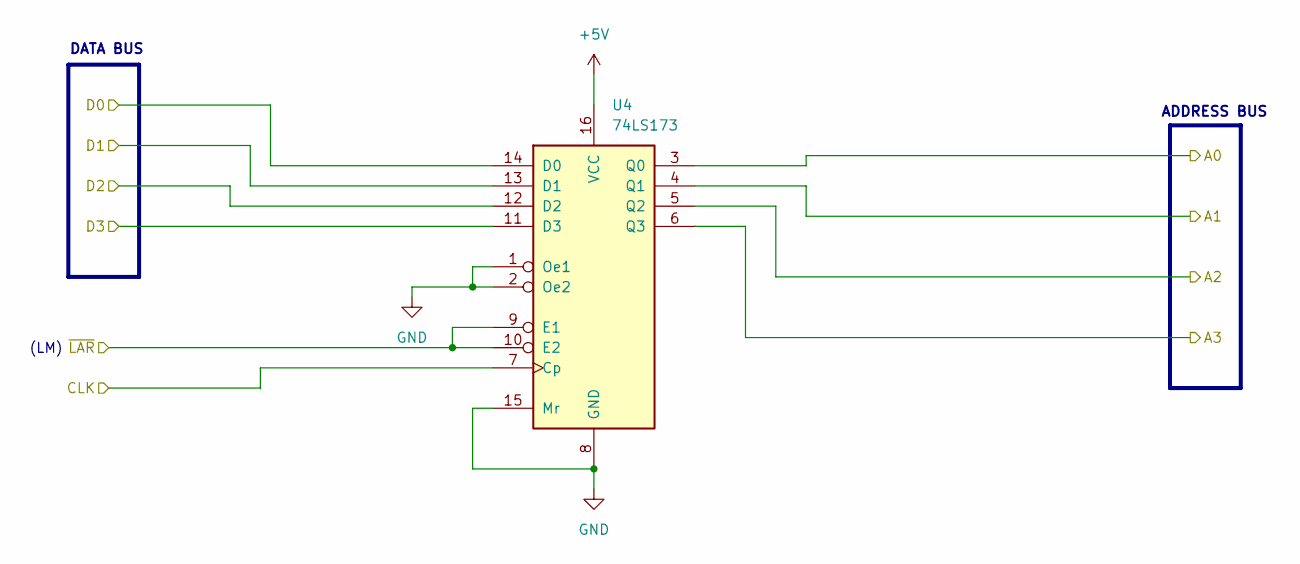
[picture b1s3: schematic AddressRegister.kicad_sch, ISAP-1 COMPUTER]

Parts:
U4: 74LS173; DIP-16_W7.62mm_LongPads

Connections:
+5V: U4.16 (VCC); also elsewhere on the board
/ALU/D0: U4.14 (D0); also elsewhere on the board
/ALU/D1: U4.13 (D1); also elsewhere on the board
/ALU/D2: U4.12 (D2); also elsewhere on the board
/ALU/D3: U4.11 (D3); also elsewhere on the board
/AddressRegister/A0: U4.3 (Q0); also elsewhere on the board
/AddressRegister/A1: U4.4 (Q1); also elsewhere on the board
/AddressRegister/A2: U4.5 (Q2); also elsewhere on the board
/AddressRegister/A3: U4.6 (Q3); also elsewhere on the board
/CLK: U4.7 (Cp); also elsewhere on the board
/~LAR: U4.9 (E1), U4.10 (E2)
GND: U4.1 (Oe1), U4.2 (Oe2), U4.8 (GND), U4.15 (Mr); also elsewhere on the board

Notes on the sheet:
DATA BUS
ADDRESS BUS
(LM)

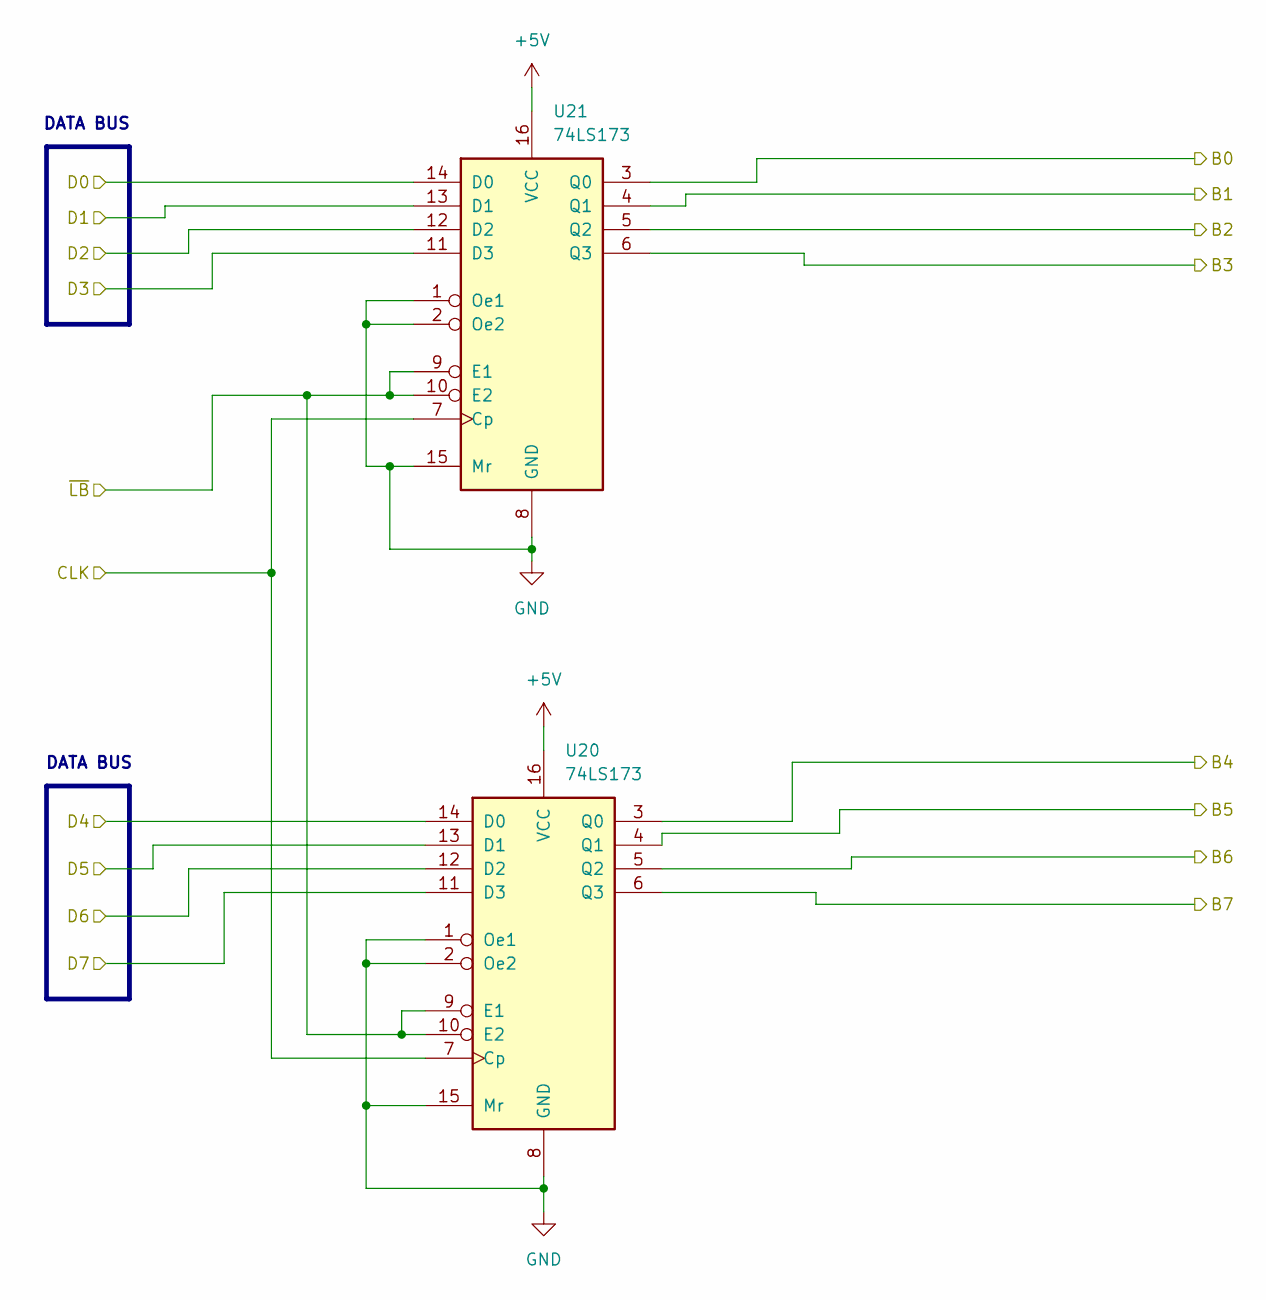
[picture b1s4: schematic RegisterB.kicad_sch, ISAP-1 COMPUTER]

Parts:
U20, U21: 74LS173; DIP-16_W7.62mm_LongPads

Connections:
+5V: U20.16 (VCC), U21.16 (VCC); also elsewhere on the board
/ALU/B0: U21.3 (Q0); also elsewhere on the board
/ALU/B1: U21.4 (Q1); also elsewhere on the board
/ALU/B2: U21.5 (Q2); also elsewhere on the board
/ALU/B3: U21.6 (Q3); also elsewhere on the board
/ALU/B4: U20.3 (Q0); also elsewhere on the board
/ALU/B5: U20.4 (Q1); also elsewhere on the board
/ALU/B6: U20.5 (Q2); also elsewhere on the board
/ALU/B7: U20.6 (Q3); also elsewhere on the board
/ALU/D0: U21.14 (D0); also elsewhere on the board
/ALU/D1: U21.13 (D1); also elsewhere on the board
/ALU/D2: U21.12 (D2); also elsewhere on the board
/ALU/D3: U21.11 (D3); also elsewhere on the board
/ALU/D4: U20.14 (D0); also elsewhere on the board
/ALU/D5: U20.13 (D1); also elsewhere on the board
/ALU/D6: U20.12 (D2); also elsewhere on the board
/ALU/D7: U20.11 (D3); also elsewhere on the board
/CLK: U20.7 (Cp), U21.7 (Cp); also elsewhere on the board
/~LB: U20.9 (E1), U20.10 (E2), U21.9 (E1), U21.10 (E2); also elsewhere on the board
GND: U20.1 (Oe1), U20.2 (Oe2), U20.8 (GND), U20.15 (Mr), U21.1 (Oe1), U21.2 (Oe2), U21.8 (GND), U21.15 (Mr); also elsewhere on the board

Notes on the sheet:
DATA BUS

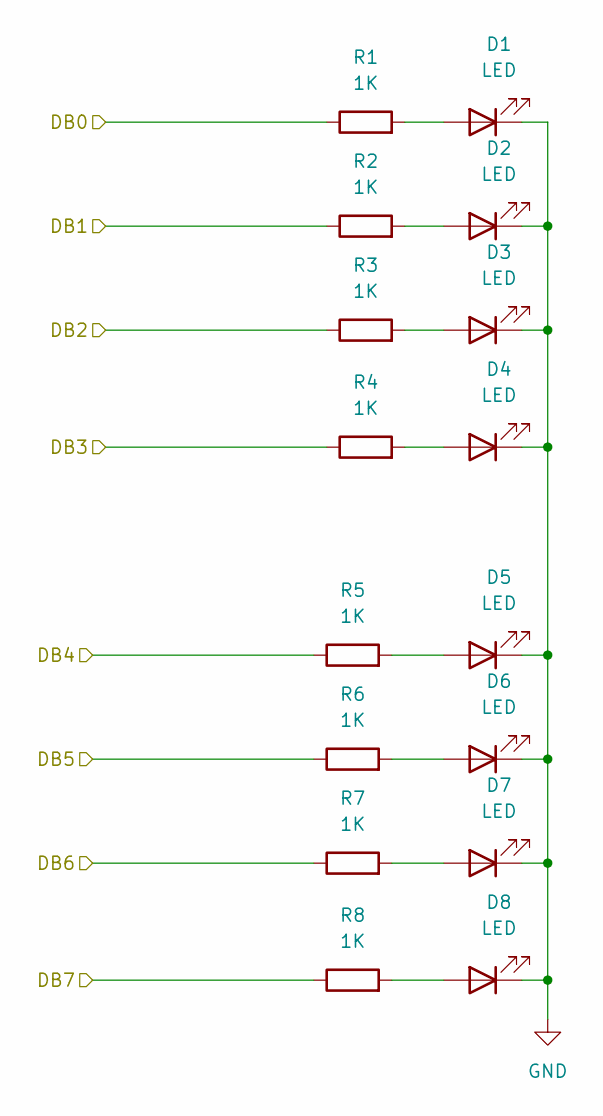
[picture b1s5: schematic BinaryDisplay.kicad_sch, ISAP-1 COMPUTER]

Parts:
D1, D2, D3, D4, D5, D6, D7, D8: LED; LED_D5.0mm
R1, R2, R3, R4, R5, R6, R7, R8: 1K; R_Axial_DIN0207_L6.3mm_D2.5mm_P7.62mm_Horizontal

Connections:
/BinaryDisplay/DB0: R1.1; also elsewhere on the board
/BinaryDisplay/DB1: R2.1; also elsewhere on the board
/BinaryDisplay/DB2: R3.1; also elsewhere on the board
/BinaryDisplay/DB3: R4.1; also elsewhere on the board
/BinaryDisplay/DB4: R5.1; also elsewhere on the board
/BinaryDisplay/DB5: R6.1; also elsewhere on the board
/BinaryDisplay/DB6: R7.1; also elsewhere on the board
/BinaryDisplay/DB7: R8.1; also elsewhere on the board
GND: D1.1 (K), D2.1 (K), D3.1 (K), D4.1 (K), D5.1 (K), D6.1 (K), D7.1 (K), D8.1 (K); also elsewhere on the board
unnamed: D1.2 (A), R1.2
unnamed: D2.2 (A), R2.2
unnamed: D3.2 (A), R3.2
unnamed: D4.2 (A), R4.2
unnamed: D5.2 (A), R5.2
unnamed: D6.2 (A), R6.2
unnamed: D7.2 (A), R7.2
unnamed: D8.2 (A), R8.2
